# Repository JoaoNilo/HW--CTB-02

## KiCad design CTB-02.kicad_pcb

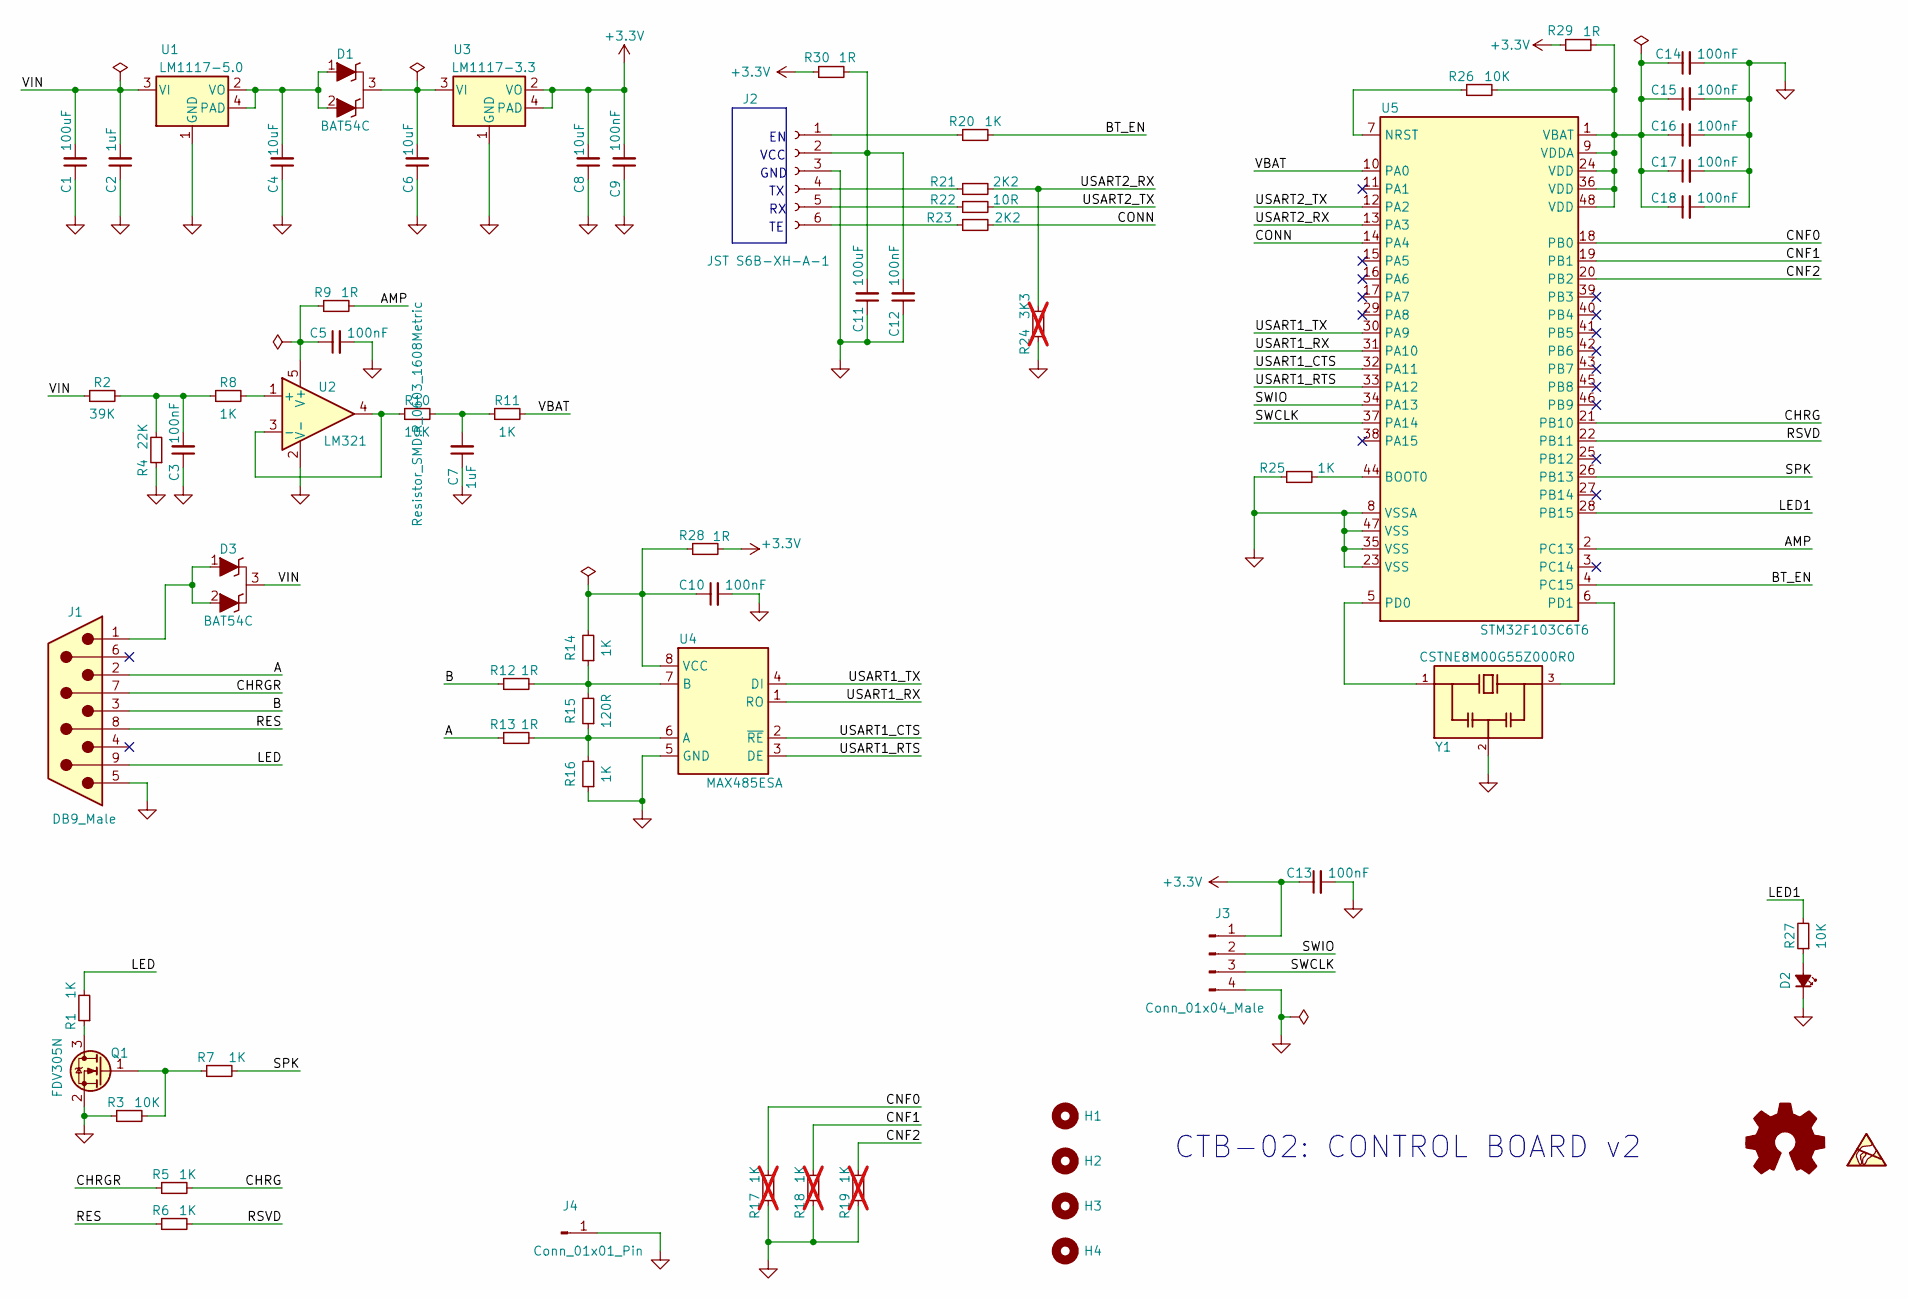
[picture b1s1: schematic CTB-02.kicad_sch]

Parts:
C1, C11: 100uF; C_1210_3225Metric
C2, C7: 1uF; C_0805_2012Metric
C3, C5, C9, C10, C12, C13, C14, C15, C16, C17, C18: 100nF; C_0603_1608Metric
C4, C6, C8: 10uF; C_1206_3216Metric
D1, D3: BAT54C; SOT-23
D2: RED 0603; LED_0603_1608Metric
H1, H2, H3, H4: MountingHole; MountingHole_2.2mm_M2
J1: DB9_Male; DSUB-9_Male_Horizontal_P2.77x2.84mm_EdgePinOffset7.70mm_Hou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
J2: JST S6B-XH-A-1; JST_S6B-XH-A-1
J3: Conn_01x04_Male; PinHeader_1x04_P2.54mm_Vertical
J4: Conn_01x01_Pin; PinHeader_1x01_P2.54mm_Vertical
LOGO1: Logo_Open_Hardware_Small; KiCad-Logo2_5mm_SilkScreen
Q1: FDV305N; SOT-23
R1, R5, R6, R7, R8, R11, R14, R16, R20, R25: 1K; R_0603_1608Metric
R2: 39K; R_0603_1608Metric
R3, R10, R26, R27: 10K; R_0603_1608Metric
R4: 22K; R_0603_1608Metric
R9, R12, R13, R28, R29, R30: 1R; R_0603_1608Metric
R15: 120R; R_0603_1608Metric
R17, R18, R19: 1K; R_0603_1608Metric; not fitted
R21, R23: 2K2; R_0603_1608Metric
R22: 10R; R_0603_1608Metric
R24: 3K3; R_0603_1608Metric; not fitted
SYM1: SYM_ESD_Small; ESD-Logo_6.6x6mm_SilkScreen
U1: LM1117-5.0; SOT-223
U2: LM321; SOT-23-5
U3: LM1117-3.3; SOT-223
U4: MAX485ESA; SOIC-8_3.9x4.9mm_P1.27mm
U5: STM32F103C6T6; LQFP-48_7x7mm_P0.5mm
Y1: CSTNE8M00G55Z000R0; OSC_CSTNE8M00G55Z000R0; PARTREV JGC42-8858A

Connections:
+3.3V: C8.2, C9.2, C13.1, J3.1, R28.2, R29.1, R30.1, U3.2 (VO), U3.4 (PAD)
/A: J1.2, R13.1
/AMP: R9.2, U5.2 (PC13)
/B: J1.3, R12.1
/BT_EN: R20.2, U5.4 (PC15)
/CHRG: R5.2, U5.21 (PB10)
/CHRGR: J1.7, R5.1
/CNF0: R17.1, U5.18 (PB0)
/CNF1: R18.2, U5.19 (PB1)
/CNF2: R19.2, U5.20 (PB2)
/CONN: R23.2, U5.14 (PA4)
/LED: J1.9, R1.2
/LED1: R27.2, U5.28 (PB15)
/RES: J1.8, R6.1
/RSVD: R6.2, U5.22 (PB11)
/SPK: R7.2, U5.26 (PB13)
/SWCLK: J3.3, U5.37 (PA14)
/SWIO: J3.2, U5.34 (PA13)
/USART1_CTS: U4.2 (~RE), U5.32 (PA11)
/USART1_RTS: U4.3 (DE), U5.33 (PA12)
/USART1_RX: U4.1 (RO), U5.31 (PA10)
/USART1_TX: U4.4 (DI), U5.30 (PA9)
/USART2_RX: R21.2, R24.2, U5.13 (PA3)
/USART2_TX: R22.2, U5.12 (PA2)
/VBAT: R11.2, U5.10 (PA0)
/VIN: C1.2, C2.2, D3.3 (K), R2.1, U1.3 (VI)
GND: C1.1, C2.1, C3.1, C4.1, C5.2, C6.1, C7.1, C8.1, C9.1, C10.2, C11.1, C12.1, C13.2, C14.2, C15.2, C16.2, C17.2, C18.2, D2.1 (K), J1.5, J2.3, J3.4, J4.1, Q1.2 (S), R3.1, R4.1, R16.1, R17.2, R18.1, R19.1, R24.1, R25.1, U1.1 (GND), U2.2 (V-), U3.1 (GND), U4.5 (GND), U5.8 (VSSA), U5.23 (VSS), U5.35 (VSS), U5.47 (VSS), Y1.2
unnamed: C3.2, R2.2, R4.2, R8.1
unnamed: C7.2, R10.2, R11.1
unnamed: C6.2, D1.3 (K), U3.3 (VI)
unnamed: D2.2 (A), R27.1
unnamed: D3.1 (A), D3.2 (A), J1.1
unnamed: J2.1, R20.1
unnamed: C11.2, C12.2, J2.2, R30.2
unnamed: J2.4, R21.1
unnamed: J2.5, R22.1
unnamed: J2.6, R23.1
unnamed: Q1.3 (D), R1.1
unnamed: Q1.1 (G), R3.2, R7.1
unnamed: C4.2, D1.1 (A), D1.2 (A), U1.2 (VO), U1.4 (PAD)
unnamed: R8.2, U2.1 (+)
unnamed: R10.1, U2.3 (-), U2.4
unnamed: C5.1, R9.1, U2.5 (V+)
unnamed: R13.2, R15.1, R16.2, U4.6 (A)
unnamed: R12.2, R14.1, R15.2, U4.7 (B)
unnamed: C10.1, R14.2, R28.1, U4.8 (VCC)
unnamed: R25.2, U5.44 (BOOT0)
unnamed: R26.1, U5.7 (NRST)
unnamed: U5.5 (PD0), Y1.1
unnamed: U5.6 (PD1), Y1.3
unnamed: C14.1, C15.1, C16.1, C17.1, C18.1, R26.2, R29.2, U5.1 (VBAT), U5.9 (VDDA), U5.24 (VDD), U5.36 (VDD), U5.48 (VDD)

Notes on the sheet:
VCC
GND
CTB-02: CONTROL BOARD v2

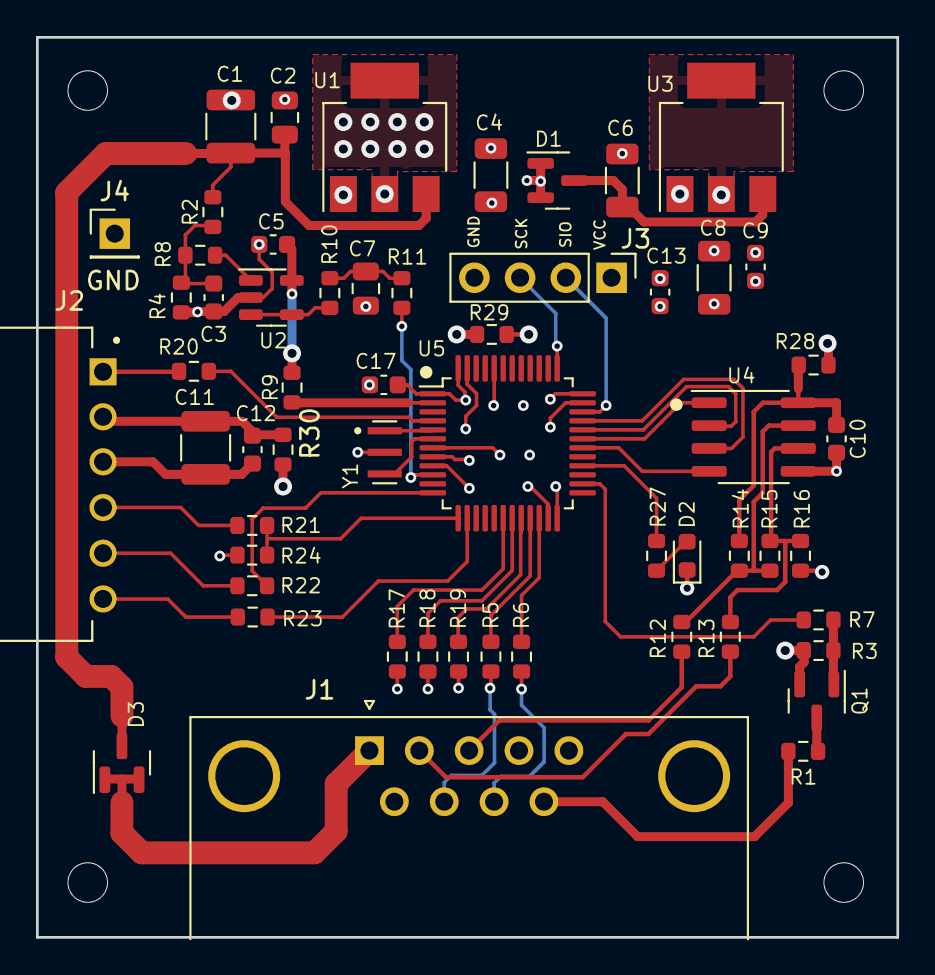
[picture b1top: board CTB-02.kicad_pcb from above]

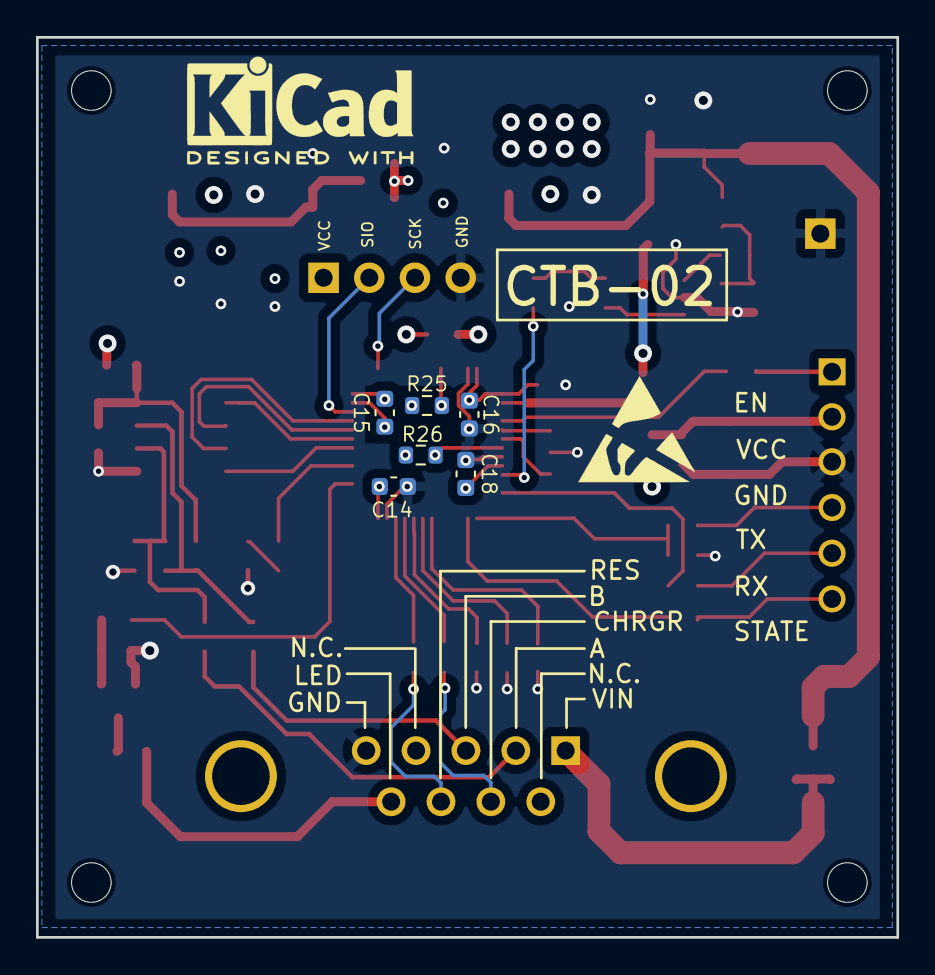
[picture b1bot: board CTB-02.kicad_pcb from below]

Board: 4 copper layers, 47.8 x 50.0 mm, 68 parts (8 on the bottom side), 51 nets.

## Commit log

2023-12-04 Initial commit.
2023-12-08 resistor R24 nao deve ser montado.
2024-08-20 last update before migrating to Gitea
